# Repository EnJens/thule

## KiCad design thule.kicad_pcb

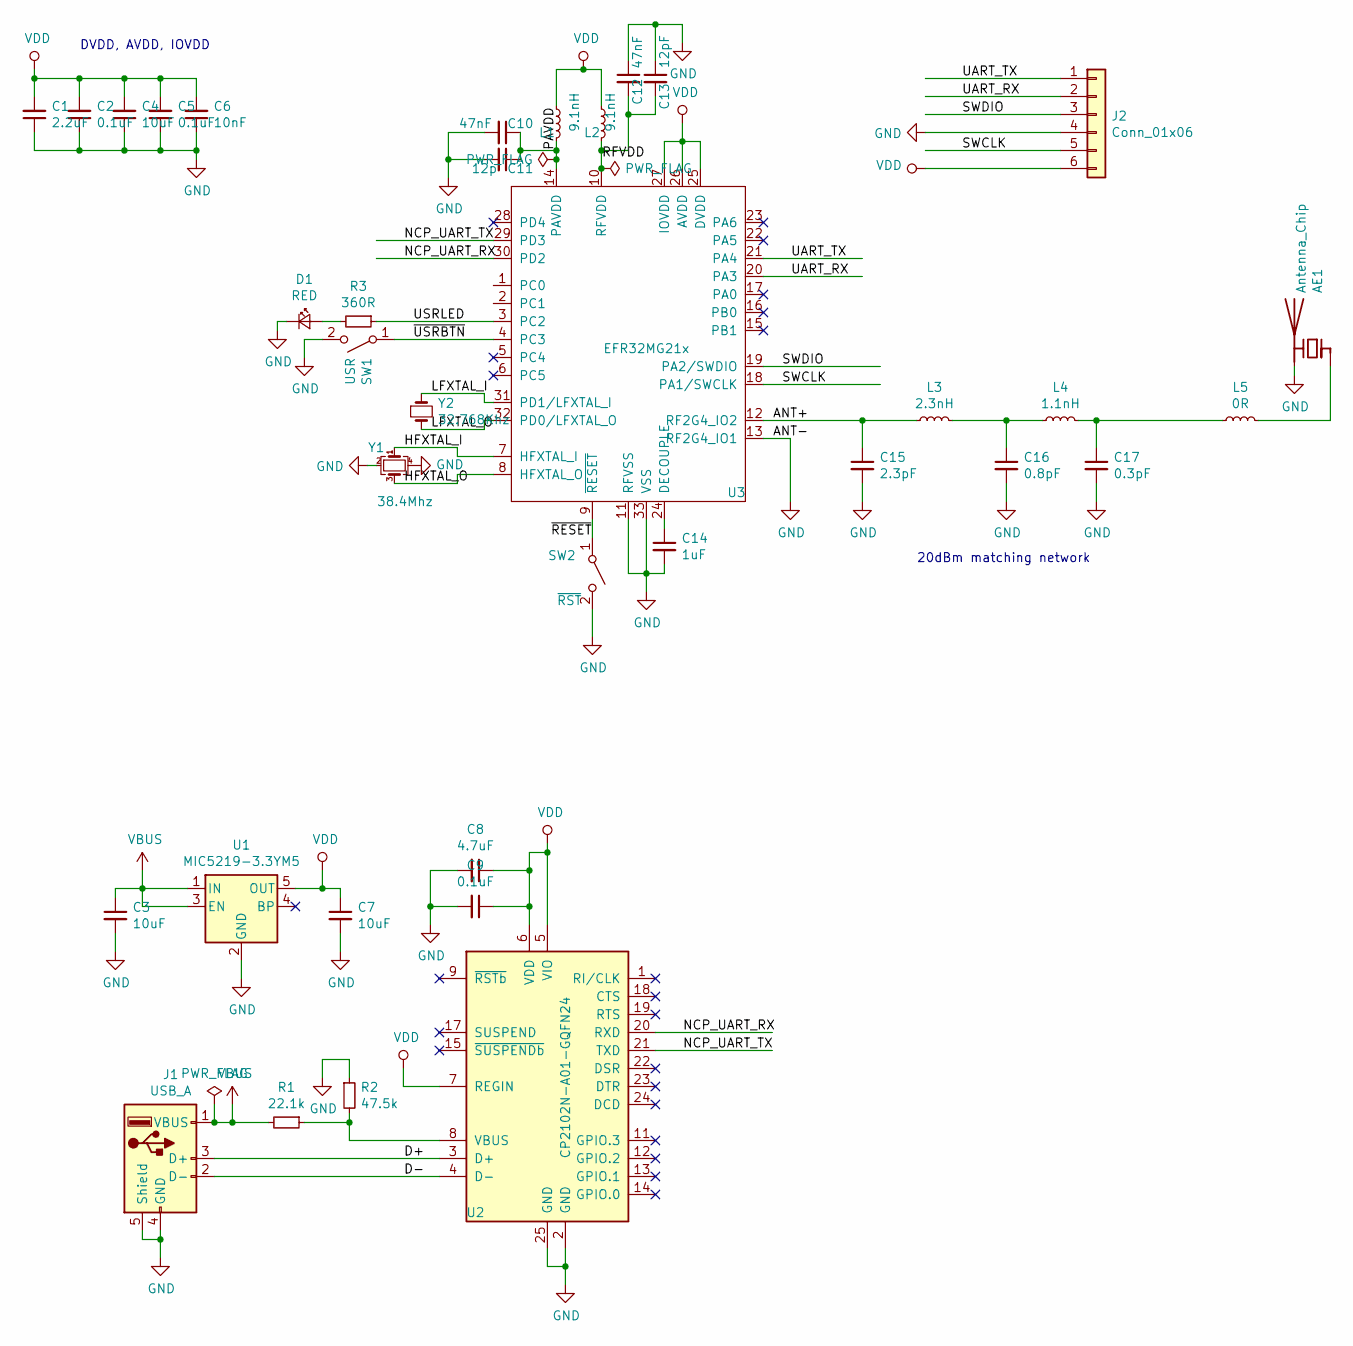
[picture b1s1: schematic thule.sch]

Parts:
AE1: Antenna_Chip; SMA_Samtec_SMA-J-P-X-ST-EM1_EdgeMount
C1: 2.2uF; C_0603_1608Metric
C2, C5, C9: 0.1uF; C_0603_1608Metric
C3, C4, C7: 10uF; C_0603_1608Metric
C6: 10nF; C_0603_1608Metric
C8: 4.7uF; C_0603_1608Metric
C10, C12: 47nF; C_0603_1608Metric
C11: 12p; C_0603_1608Metric
C13: 12pF; C_0603_1608Metric
C14: 1uF; C_0603_1608Metric
C15: 2.3pF; C_0402_1005Metric
C16: 0.8pF; C_0402_1005Metric
C17: 0.3pF; C_0402_1005Metric
D1: RED; LED_0603_1608Metric
J1: USB_A; USB_A_CNCTech_1001-011-01101_Horizontal
J2: Conn_01x06; PinHeader_1x06_P2.54mm_Vertical
L1, L2: 9.1nH; L_0402_1005Metric; LCSC C281011
L3: 2.3nH; L_0402_1005Metric
L4: 1.1nH; L_0402_1005Metric
L5: 0R; L_0402_1005Metric
R1: 22.1k; R_0603_1608Metric
R2: 47.5k; R_0603_1608Metric
R3: 360R; R_0603_1608Metric
SW1: USR; SW_SPST_B3U-1000P
SW2: ~RST~; SW_SPST_B3U-1000P
U1: MIC5219-3.3YM5; SOT-23-5
U2: CP2102N-A01-GQFN24; QFN-24-1EP_4x4mm_P0.5mm_EP2.6x2.6mm
U3: EFR32MG21x; QFN-32-1EP_4x4mm_P0.4mm_EP2.65x2.65mm
Y1: 38.4Mhz; Crystal_SMD_3225-4Pin_3.2x2.5mm; Mouser 520-384-10-33B-CKYT
Y2: 32.768Khz; Crystal_SMD_2012-2Pin_2.0x1.2mm; Mouser 520-.327-12.5-12R-T

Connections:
/ANT+: C15.1, L3.1, U3.12 (RF2G4_IO2)
/D+: J1.3 (D+), U2.3 (D+)
/D-: J1.2 (D-), U2.4 (D-)
/HFXTAL_I: U3.7 (HFXTAL_I), Y1.1
/HFXTAL_O: U3.8 (HFXTAL_O), Y1.3
/LFXTAL_I: U3.31 (PD1/LFXTAL_I), Y2.1
/LFXTAL_O: U3.32 (PD0/LFXTAL_O), Y2.2
/NCP_UART_RX: U2.20 (RXD), U3.30 (PD2)
/NCP_UART_TX: U2.21 (TXD), U3.29 (PD3)
/PAVDD: C10.1, C11.1, L1.2, U3.14 (PAVDD)
/RFVDD: C12.2, C13.2, L2.2, U3.10 (RFVDD)
/SWCLK: J2.5, U3.18 (PA1/SWCLK)
/SWDIO: J2.3, U3.19 (PA2/SWDIO)
/UART_RX: J2.2, U3.20 (PA3)
/UART_TX: J2.1, U3.21 (PA4)
/USRLED: R3.1, U3.3 (PC2)
/~RESET~: SW2.1 (A), U3.9 (~RESET)
/~USRBTN~: SW1.1 (A), U3.4 (PC3)
GND: AE1.2 (PCB_Trace), C1.1, C2.1, C3.2, C4.1, C5.1, C6.1, C7.2, C8.2, C9.2, C10.2, C11.2, C12.1, C13.1, C14.2, C15.2, C16.2, C17.2, D1.1 (K), J1.4 (GND), J1.5 (Shield), J2.4, R2.1, SW1.2 (B), SW2.2 (B), U1.2 (GND), U2.2 (GND), U2.25 (GND), U3.11 (RFVSS), U3.13 (RF2G4_IO1), U3.33 (VSS), Y1.2, Y1.4
unnamed: AE1.1 (FEED), L5.2
unnamed: C14.1, U3.24 (DECOUPLE)
unnamed: C16.1, L3.2, L4.1
unnamed: C17.1, L4.2, L5.1
unnamed: D1.2 (A), R3.2
unnamed: R1.1, R2.2, U2.8 (VBUS)
VBUS: C3.1, J1.1 (VBUS), R1.2, U1.1 (IN), U1.3 (EN)
VDD: C1.2, C2.2, C4.2, C5.2, C6.2, C7.1, C8.1, C9.1, J2.6, L1.1, L2.1, U1.5 (OUT), U2.5 (VIO), U2.6 (VDD), U2.7 (REGIN), U3.25 (DVDD), U3.26 (AVDD), U3.27 (IOVDD)

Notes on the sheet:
DVDD, AVDD, IOVDD
20dBm matching network

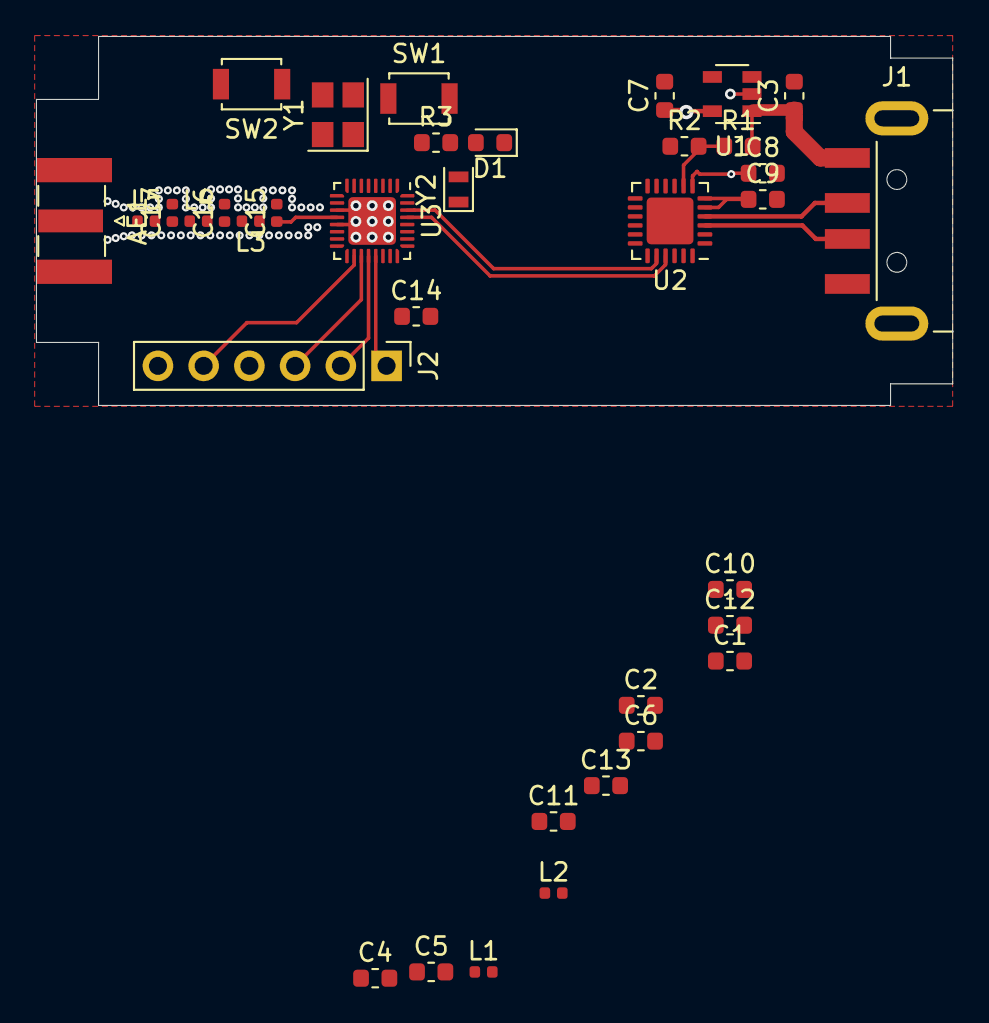
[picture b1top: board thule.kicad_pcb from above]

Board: 4 copper layers, 50.9 x 20.5 mm, 36 parts (0 on the bottom side), 27 nets.

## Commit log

2020-02-17 Initial board, WIP
2020-02-18 Start routing, use bigger packages
2020-02-18 Add enclosure step file
